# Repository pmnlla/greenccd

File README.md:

# greenCCD
A theoretical implementation of the SuzyQable as a USBC-USBC dongle.

## Why?

- The original SuzyQable was discontinued.
- Most implimentations on the market forgo the internal USB hub.
- Most implimentations on the market also suck.

## Internal USB hub??? Why?

The original SuzyQable, manufactured by sparkfun, contained a USB hub in order to mount a target CrOS device twice on the host machine:

1. As a TTL interface to the Cr50 or Ti50
2. As a target _android_ device for usage with ADB.

The ADB system is also used to (debug android apps on ChromeOS)[https://chromeos.dev/en/android-environment/deploying-apps], hence its neccesity.

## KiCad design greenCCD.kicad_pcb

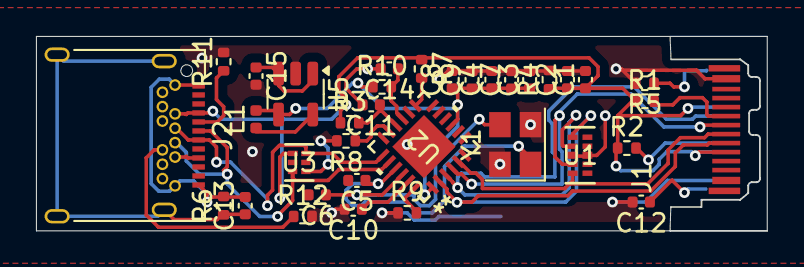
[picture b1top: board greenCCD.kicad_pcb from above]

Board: 2 copper layers, 40.5 x 10.8 mm, 35 parts (0 on the bottom side), 26 nets.

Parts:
C1, C3: 0,1uF; C_0402_1005Metric
C2, C4, C7, C14: 1uF; C_0402_1005Metric
C5, C6, C11: TBD; C_0402_1005Metric
C8, C9, C10, C12, C13: 0.1uF; C_0402_1005Metric
C15: C_Small; C_0402_1005Metric
J1: USB_C_Receptacle; USB_C_Plug_JAE_DX07P024AJ1
J2: USB_C_Receptacle_USB2.0_14P; USB_C_Receptacle_Amphenol_12401548E4-2A
L1: 10uH; L_0402_1005Metric
R1, R2, R3: R_Small; R_0402_1005Metric
R4: 100kR; R_0402_1005Metric
R5, R6: 330R; R_0402_1005Metric
R7, R8: 10kR; R_0402_1005Metric
R9: 12k/1%; R_0402_1005Metric
R10: 10k; R_0402_1005Metric
R11, R12: 5k1; R_0402_1005Metric
U1: TPD4EUSB30DQAR; DQA10
U2: USB2422/MJ; SQFN24_4X4MC_MCH
U3: TPD2E001DRYR; DRY6
U5: TPS62203DBV; SOT-23-5
Y1: Crystal_GND24_Small; Crystal_SMD_3225-4Pin_3.2x2.5mm

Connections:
+3V3: C3.1, C4.1, C7.1, C8.1, C9.1, L1.2, R10.1, U2.1 (VDD33), U2.9 (VDD33), U5.4 (FB)
+5V: C1.1, C2.1, J1.A4 (VBUS), J1.A9 (VBUS), J1.B4 (VBUS), J1.B9 (VBUS), J2.A4 (VBUS), J2.A9 (VBUS), J2.B4 (VBUS), J2.B9 (VBUS), R1.1, R2.1, R3.1, R4.1, R7.1, U3.1 (VCC)
/HUB_RST: C14.1, R10.2, U2.15 (RESET_N)
/TDP4P6: J1.A7 (D-), U1.5, U2.5 (USBDM_DN2/PRT_DIS_P2)
/TPD4P7: J1.A6 (D+), U1.4, U2.4 (USBDP_DN1/PRT_DIS_M2)
/USB_DN_N1: J1.B8 (SBU2), U1.2, U2.3 (USBDP_DN1/PRT_DIS_P1)
/USB_DN_P1: J1.A8 (SBU1), U1.1, U2.2 (USBDP_DN1/PRT_DIS_M1)
/USB_UP_N: J2.A7 (D-), J2.B7 (D-), U2.19 (USBDM_UP), U3.6 (IO2)
/USB_UP_P: J2.A6 (D+), J2.B6 (D+), U2.20 (USBDP_UP), U3.3 (IO1)
GND: C1.2, C2.2, C3.2, C4.2, C7.2, C8.2, C9.2, C10.2, C11.2, C12.2, C14.2, C15.2, J1.A1 (GND), J1.A12 (GND), J1.B1 (GND), J1.B12 (GND), R4.2, R5.2, R8.2, R9.1, R11.2, R12.2, U1.3, U1.8, U2.25 (EPAD), U3.4 (GND), U5.2 (GND), Y1.2, Y1.4
unnamed: C13.2, J2.A1 (GND), J2.A12 (GND), J2.B1 (GND), J2.B12 (GND), R6.2
unnamed: J1.A5 (CC1), R1.2
unnamed: J1.B5 (CC2), R2.2
unnamed: C12.1, J1.S1 (SHIELD), R5.1
unnamed: J2.A5 (CC1), R11.1
unnamed: J2.B5 (CC2), R12.1
unnamed: C13.1, J2.S1 (SHIELD), R6.1
unnamed: C10.1, U2.23 (PLLFILT)
unnamed: R9.2, U2.24 (RBIAS)
unnamed: R7.2, U2.13 (SMBDATA/NON_REM1)
unnamed: R8.1, U2.17 (SUSP_IND/LOCAL_PWR*NON_REM0)
unnamed: C11.1, R3.2, U2.16 (VBUS_DET)
unnamed: C6.1, U2.22 (XTALIN/CLKIN), Y1.3
unnamed: C5.1, U2.21 (XTALOUT*(CLKIN_EN)), Y1.1
unnamed: C15.1, U5.1 (VI), U5.3 (EN)
unnamed: L1.1, U5.5 (SW)

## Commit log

2024-08-27 init!
2024-09-11 add voltage regulator
